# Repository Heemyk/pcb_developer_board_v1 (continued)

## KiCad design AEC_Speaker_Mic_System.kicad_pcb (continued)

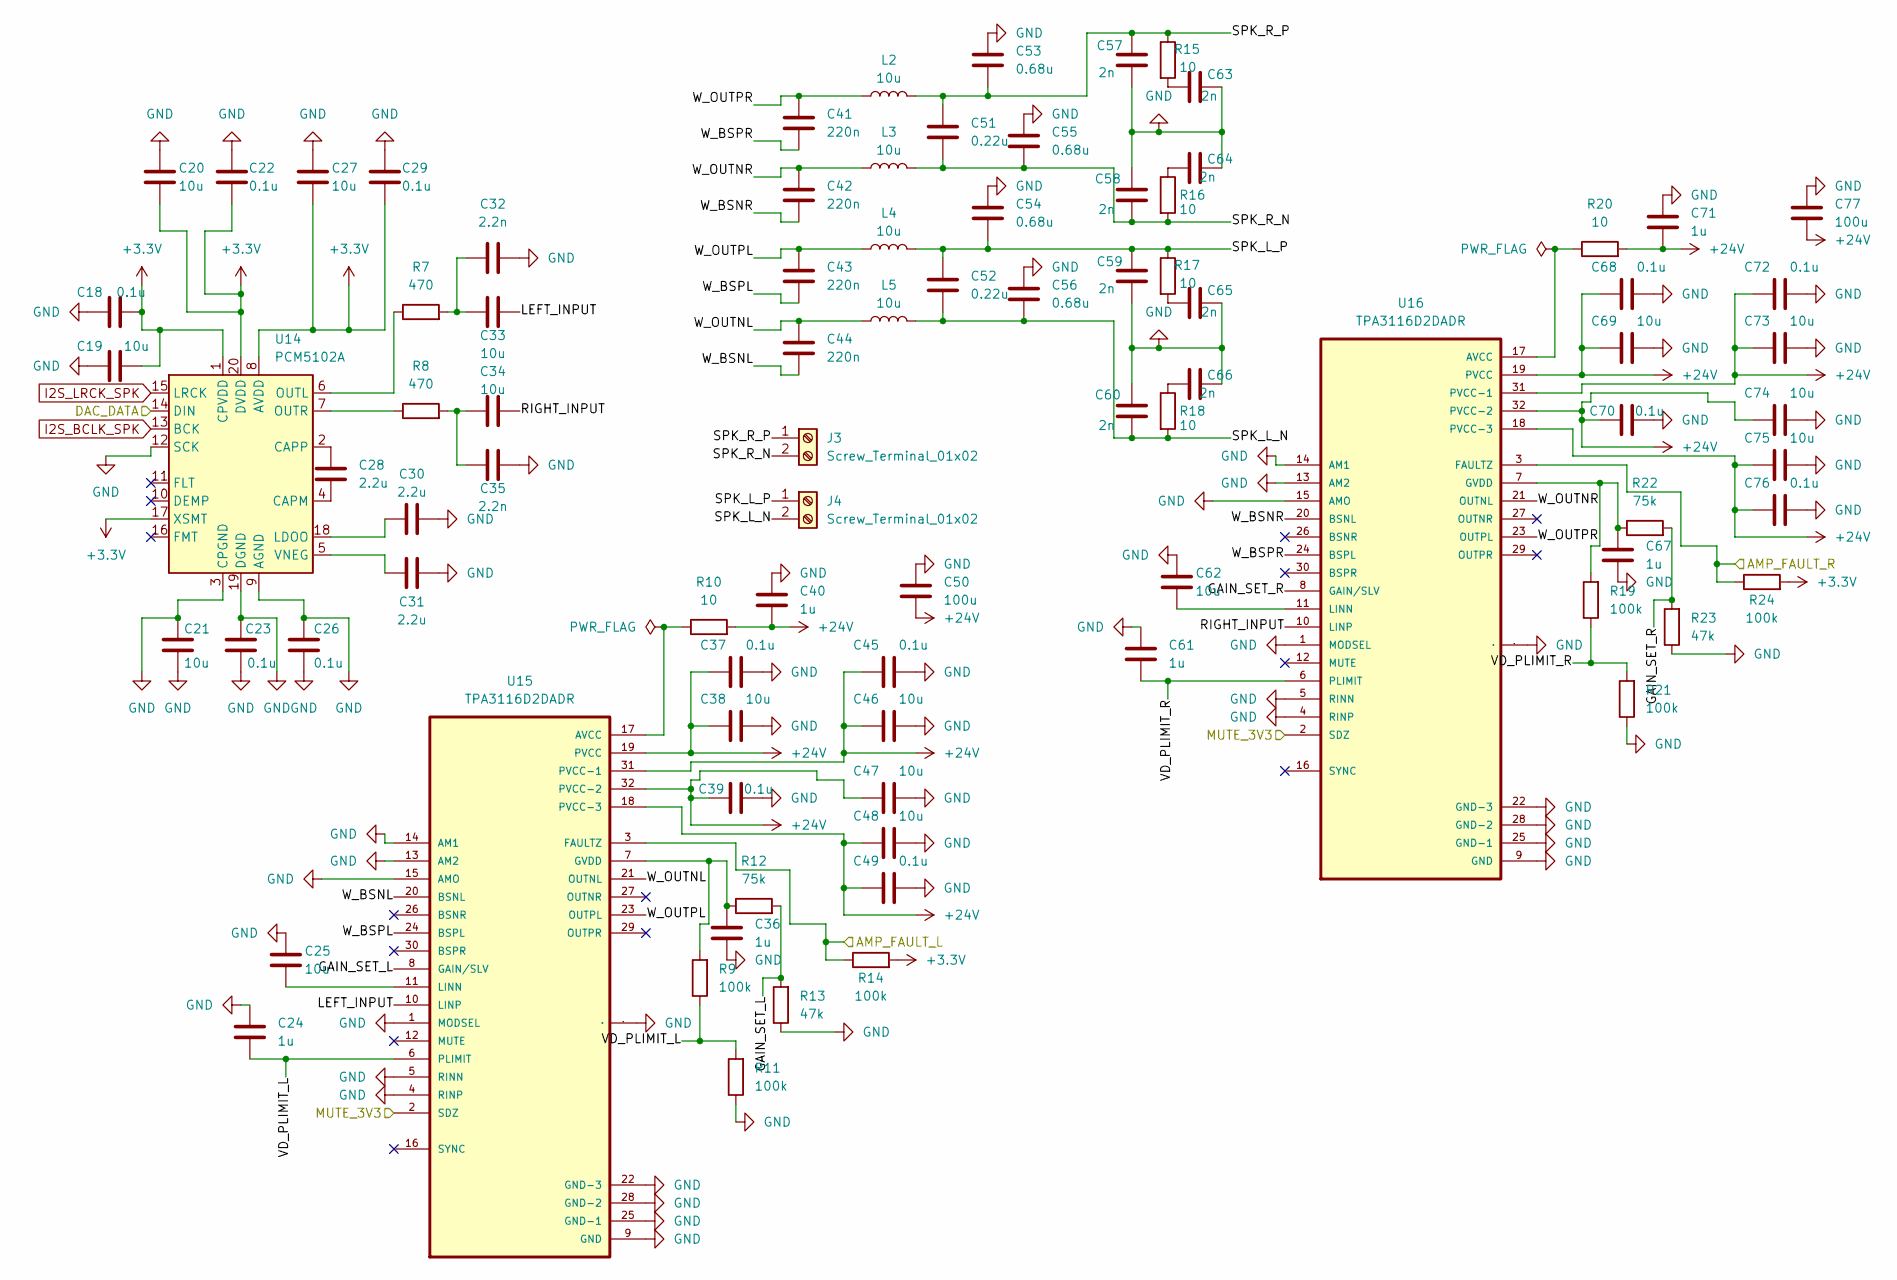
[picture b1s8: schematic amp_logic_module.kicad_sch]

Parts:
C18, C22, C23, C26, C29, C37, C39, C45, C49, C68, C70, C72, C76: 0.1u; C_0603_1608Metric
C19, C20, C21, C25, C27, C33, C34, C38, C46, C47, C48, C62, C69, C73, C74, C75: 10u; C_0603_1608Metric
C24, C36, C40, C61, C67, C71: 1u; C_0603_1608Metric
C28, C30, C31: 2.2u; C_0603_1608Metric
C32, C35: 2.2n; C_0603_1608Metric
C41, C42, C43, C44: 220n; C_0603_1608Metric
C50, C77: 100u; C_0603_1608Metric
C51, C52: 0.22u; C_0603_1608Metric
C53, C54, C55, C56: 0.68u; C_0603_1608Metric
C57, C58, C59, C60, C63, C64, C65, C66: 2n; C_0805_2012Metric; LCSC Part # C1656
J3, J4: Screw_Terminal_01x02; CONN-TH_2P-P5.00_WJ500V-5.08-2P; LCSC Part # C8465
L2: 10u; IND-SMD_L10.4-W10.3; LCSC C9935
L3, L4, L5: 10u; IND-SMD_L10.4-W10.3
R7, R8: 470; R_0603_1608Metric
R9, R11, R14, R19, R21, R24: 100k; R_0603_1608Metric
R10, R15, R16, R17, R18, R20: 10; R_0805_2012Metric
R12, R22: 75k; R_0603_1608Metric
R13: 47k; R_0603_1608Metric
R23: 47k; R_0603_1608Metric; LCSC Part # C25819
U14: PCM5102A; TSSOP-20_4.4x6.5mm_P0.65mm; LCSC Part # C107671
U15, U16: TPA3116D2DADR; SOP65P810X115-33N

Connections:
+3.3V: C18.2, C19.2, C20.2, C22.2, C27.2, C29.2, R14.2, R24.2, U14.1 (CPVDD), U14.8 (AVDD), U14.17 (XSMT), U14.20 (DVDD); also elsewhere on the board
+24V: C37.2, C38.2, C39.2, C40.2, C45.2, C46.2, C47.2, C48.2, C49.2, C50.2, C68.2, C69.2, C70.2, C71.2, C72.2, C73.2, C74.2, C75.2, C76.2, C77.2, R10.2, R20.2, U15.18 (PVCC-3), U15.19 (PVCC), U15.31 (PVCC-1), U15.32 (PVCC-2), U16.18 (PVCC-3), U16.19 (PVCC), U16.31 (PVCC-1), U16.32 (PVCC-2); also elsewhere on the board
/PCB_Control/AMP_FAULT_1: R14.1, U15.3 (FAULTZ); also elsewhere on the board
/PCB_Control/AMP_FAULT_2: R24.1, U16.3 (FAULTZ); also elsewhere on the board
/PCB_Control/Amp_Control_Module_12/GAIN_SET_L: R12.2, R13.2, U15.8 (GAIN/SLV)
/PCB_Control/Amp_Control_Module_12/GAIN_SET_R: R22.2, R23.2, U16.8 (GAIN/SLV)
/PCB_Control/Amp_Control_Module_12/LEFT_INPUT: C33.2, U15.10 (LINP)
/PCB_Control/Amp_Control_Module_12/RIGHT_INPUT: C34.2, U16.10 (LINP)
/PCB_Control/Amp_Control_Module_12/SPK_L_N: C52.2, C56.2, C60.2, J4.2, L5.2, R18.2
/PCB_Control/Amp_Control_Module_12/SPK_L_P: C52.1, C54.2, C59.1, J4.1, L4.2, R17.1
/PCB_Control/Amp_Control_Module_12/SPK_R_N: C51.2, C55.2, C58.2, J3.2, L3.2, R16.2
/PCB_Control/Amp_Control_Module_12/SPK_R_P: C51.1, C53.2, C57.1, J3.1, L2.2, R15.1
/PCB_Control/Amp_Control_Module_12/VD_PLIMIT_L: C24.1, R9.1, R11.2, U15.6 (PLIMIT)
/PCB_Control/Amp_Control_Module_12/VD_PLIMIT_R: C61.1, R19.1, R21.2, U16.6 (PLIMIT)
/PCB_Control/Amp_Control_Module_12/W_BSNL: C44.1, U15.20 (BSNL)
/PCB_Control/Amp_Control_Module_12/W_BSNR: C42.1, U16.20 (BSNL)
/PCB_Control/Amp_Control_Module_12/W_BSPL: C43.1, U15.24 (BSPL)
/PCB_Control/Amp_Control_Module_12/W_BSPR: C41.1, U16.24 (BSPL)
/PCB_Control/Amp_Control_Module_12/W_OUTNL: C44.2, L5.1, U15.21 (OUTNL)
/PCB_Control/Amp_Control_Module_12/W_OUTNR: C42.2, L3.1, U16.21 (OUTNL)
/PCB_Control/Amp_Control_Module_12/W_OUTPL: C43.2, L4.1, U15.23 (OUTPL)
/PCB_Control/Amp_Control_Module_12/W_OUTPR: C41.2, L2.1, U16.23 (OUTPL)
/PCB_Control/DAC_DATA_12: U14.14 (DIN); also elsewhere on the board
/PCB_Control/MUTE_3V3: U15.2 (SDZ), U16.2 (SDZ); also elsewhere on the board
GND: C18.1, C19.1, C20.1, C21.1, C21.2, C22.1, C23.1, C23.2, C24.2, C25.1, C26.1, C26.2, C27.1, C29.1, C30.1, C31.1, C32.2, C35.2, C36.2, C37.1, C38.1, C39.1, C40.1, C45.1, C46.1, C47.1, C48.1, C49.1, C50.1, C53.1, C54.1, C55.1, C56.1, C57.2, C58.1, C59.2, C60.1, C61.2, C62.1, C63.2, C64.2, C65.2, C66.2, C67.2, C68.1, C69.1, C70.1, C71.1, C72.1, C73.1, C74.1, C75.1, C76.1, C77.1, R11.1, R13.1, R21.1, R23.1, U14.3 (CPGND), U14.9 (AGND), U14.12 (SCK), U14.19 (DGND), U15.1 (MODSEL), U15.4 (RINP), U15.5 (RINN), U15.9 (GND), U15.13 (AM2), U15.14 (AM1), U15.15 (AMO), U15.22 (GND-3), U15.25 (GND-1), U15.28 (GND-2), U15.33 (PAD), U16.1 (MODSEL), U16.4 (RINP), U16.5 (RINN), U16.9 (GND), U16.13 (AM2), U16.14 (AM1), U16.15 (AMO), U16.22 (GND-3), U16.25 (GND-1), U16.28 (GND-2), U16.33 (PAD); also elsewhere on the board
I2S_BCLK_SPK: U14.13 (BCK); also elsewhere on the board
I2S_LRCK_SPK: U14.15 (LRCK); also elsewhere on the board
unnamed: C32.1, C33.1, R7.2
unnamed: C34.1, C35.1, R8.2
unnamed: C63.1, R15.2
unnamed: C64.1, R16.1
unnamed: C65.1, R17.2
unnamed: C66.1, R18.1
unnamed: C28.2, U14.4 (CAPM)
unnamed: C28.1, U14.2 (CAPP)
unnamed: C30.2, U14.18 (LDOO)
unnamed: R7.1, U14.6 (OUTL)
unnamed: R8.1, U14.7 (OUTR)
unnamed: C31.2, U14.5 (VNEG)
unnamed: R10.1, U15.17 (AVCC)
unnamed: C36.1, R9.2, R12.1, U15.7 (GVDD)
unnamed: C25.2, U15.11 (LINN)
unnamed: R20.1, U16.17 (AVCC)
unnamed: C67.1, R19.2, R22.1, U16.7 (GVDD)
unnamed: C62.2, U16.11 (LINN)

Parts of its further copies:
C78, C82, C83, C86, C89, C97, C99, C105, C109, C128, C130, C132, C136, C138, C142, C143, C146, C149, C157, C159, C165, C169, C188, C190, C192, C196, C198, C202, C203, C206, C209, C217, C219, C225, C229, C248, C250, C252, C256: 0.1u; C_0603_1608Metric
C79, C80, C81, C85, C87, C93, C94, C98, C106, C107, C108, C122, C129, C133, C134, C135, C139, C140, C141, C145, C147, C153, C154, C158, C166, C167, C168, C182, C189, C193, C194, C195, C199, C200, C201, C205, C207, C213, C214, C218, C226, C227, C228, C242, C249, C253, C254, C255: 10u; C_0603_1608Metric
C84, C96, C100, C121, C127, C131, C144, C156, C160, C181, C187, C191, C204, C216, C220, C241, C247, C251: 1u; C_0603_1608Metric
C88, C90, C91, C148, C150, C151, C208, C210, C211: 2.2u; C_0603_1608Metric
C92, C95, C152, C155, C212, C215: 2.2n; C_0603_1608Metric
C101, C102, C103, C104, C161, C162, C163, C164, C221, C222, C223, C224: 220n; C_0603_1608Metric
C110, C137, C170, C197, C230, C257: 100u; C_0603_1608Metric
C111, C112, C171, C172, C231, C232: 0.22u; C_0603_1608Metric
C113, C114, C115, C116, C173, C174, C175, C176, C233, C234, C235, C236: 0.68u; C_0603_1608Metric
C117, C118, C119, C120, C123, C124, C125, C126, C177, C178, C179, C180, C183, C184, C185, C186, C237, C238, C239, C240, C243, C244, C245, C246: 2n; C_0805_2012Metric; LCSC Part # C1656
J5, J6, J7, J8, J9, J10: Screw_Terminal_01x02; CONN-TH_2P-P5.00_WJ500V-5.08-2P; LCSC Part # C8465
L6, L10, L14: 10u; IND-SMD_L10.4-W10.3; LCSC C9935
L7, L8, L9, L11, L12, L13, L15, L16, L17: 10u; IND-SMD_L10.4-W10.3
R25, R26, R43, R44, R61, R62: 470; R_0603_1608Metric
R27, R29, R32, R37, R39, R42, R45, R47, R50, R55, R57, R60, R63, R65, R68, R73, R75, R78: 100k; R_0603_1608Metric
R28, R33, R34, R35, R36, R38, R46, R51, R52, R53, R54, R56, R64, R69, R70, R71, R72, R74: 10; R_0805_2012Metric
R30, R40, R48, R58, R66, R76: 75k; R_0603_1608Metric
R31, R49, R67: 47k; R_0603_1608Metric
R41, R59, R77: 47k; R_0603_1608Metric; LCSC Part # C25819
U17, U20, U23: PCM5102A; TSSOP-20_4.4x6.5mm_P0.65mm; LCSC Part # C107671
U18, U19, U21, U22, U24, U25: TPA3116D2DADR; SOP65P810X115-33N

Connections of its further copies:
+3.3V: C78.2, C79.2, C80.2, C82.2, C87.2, C89.2, C138.2, C139.2, C140.2, C142.2, C147.2, C149.2, C198.2, C199.2, C200.2, C202.2, C207.2, C209.2, R32.2, R42.2, R50.2, R60.2, R68.2, R78.2, U17.1 (CPVDD), U17.8 (AVDD), U17.17 (XSMT), U17.20 (DVDD), U20.1 (CPVDD), U20.8 (AVDD), U20.17 (XSMT), U20.20 (DVDD), U23.1 (CPVDD), U23.8 (AVDD), U23.17 (XSMT), U23.20 (DVDD); also elsewhere on the board
+24V: C97.2, C98.2, C99.2, C100.2, C105.2, C106.2, C107.2, C108.2, C109.2, C110.2, C128.2, C129.2, C130.2, C131.2, C132.2, C133.2, C134.2, C135.2, C136.2, C137.2, C157.2, C158.2, C159.2, C160.2, C165.2, C166.2, C167.2, C168.2, C169.2, C170.2, C188.2, C189.2, C190.2, C191.2, C192.2, C193.2, C194.2, C195.2, C196.2, C197.2, C217.2, C218.2, C219.2, C220.2, C225.2, C226.2, C227.2, C228.2, C229.2, C230.2, C248.2, C249.2, C250.2, C251.2, C252.2, C253.2, C254.2, C255.2, C256.2, C257.2, R28.2, R38.2, R46.2, R56.2, R64.2, R74.2, U18.18 (PVCC-3), U18.19 (PVCC), U18.31 (PVCC-1), U18.32 (PVCC-2), U19.18 (PVCC-3), U19.19 (PVCC), U19.31 (PVCC-1), U19.32 (PVCC-2), U21.18 (PVCC-3), U21.19 (PVCC), U21.31 (PVCC-1), U21.32 (PVCC-2), U22.18 (PVCC-3), U22.19 (PVCC), U22.31 (PVCC-1), U22.32 (PVCC-2), U24.18 (PVCC-3), U24.19 (PVCC), U24.31 (PVCC-1), U24.32 (PVCC-2), U25.18 (PVCC-3), U25.19 (PVCC), U25.31 (PVCC-1), U25.32 (PVCC-2); also elsewhere on the board
/PCB_Control/AMP_FAULT_3: R32.1, U18.3 (FAULTZ); also elsewhere on the board
/PCB_Control/AMP_FAULT_4: R42.1, U19.3 (FAULTZ); also elsewhere on the board
/PCB_Control/AMP_FAULT_5: R50.1, U21.3 (FAULTZ); also elsewhere on the board
/PCB_Control/AMP_FAULT_6: R60.1, U22.3 (FAULTZ); also elsewhere on the board
/PCB_Control/AMP_FAULT_7: R68.1, U24.3 (FAULTZ); also elsewhere on the board
/PCB_Control/AMP_FAULT_8: R78.1, U25.3 (FAULTZ); also elsewhere on the board
/PCB_Control/Amp_Control_Module_34/GAIN_SET_L: R30.2, R31.2, U18.8 (GAIN/SLV)
/PCB_Control/Amp_Control_Module_34/GAIN_SET_R: R40.2, R41.2, U19.8 (GAIN/SLV)
/PCB_Control/Amp_Control_Module_34/LEFT_INPUT: C93.2, U18.10 (LINP)
/PCB_Control/Amp_Control_Module_34/RIGHT_INPUT: C94.2, U19.10 (LINP)
/PCB_Control/Amp_Control_Module_34/SPK_L_N: C112.2, C116.2, C120.2, J6.2, L9.2, R36.2
/PCB_Control/Amp_Control_Module_34/SPK_L_P: C112.1, C114.2, C119.1, J6.1, L8.2, R35.1
/PCB_Control/Amp_Control_Module_34/SPK_R_N: C111.2, C115.2, C118.2, J5.2, L7.2, R34.2
/PCB_Control/Amp_Control_Module_34/SPK_R_P: C111.1, C113.2, C117.1, J5.1, L6.2, R33.1
/PCB_Control/Amp_Control_Module_34/VD_PLIMIT_L: C84.1, R27.1, R29.2, U18.6 (PLIMIT)
/PCB_Control/Amp_Control_Module_34/VD_PLIMIT_R: C121.1, R37.1, R39.2, U19.6 (PLIMIT)
/PCB_Control/Amp_Control_Module_34/W_BSNL: C104.1, U18.20 (BSNL)
/PCB_Control/Amp_Control_Module_34/W_BSNR: C102.1, U19.20 (BSNL)
/PCB_Control/Amp_Control_Module_34/W_BSPL: C103.1, U18.24 (BSPL)
/PCB_Control/Amp_Control_Module_34/W_BSPR: C101.1, U19.24 (BSPL)
/PCB_Control/Amp_Control_Module_34/W_OUTNL: C104.2, L9.1, U18.21 (OUTNL)
/PCB_Control/Amp_Control_Module_34/W_OUTNR: C102.2, L7.1, U19.21 (OUTNL)
/PCB_Control/Amp_Control_Module_34/W_OUTPL: C103.2, L8.1, U18.23 (OUTPL)
/PCB_Control/Amp_Control_Module_34/W_OUTPR: C101.2, L6.1, U19.23 (OUTPL)
/PCB_Control/Amp_Control_Module_56/GAIN_SET_L: R48.2, R49.2, U21.8 (GAIN/SLV)
/PCB_Control/Amp_Control_Module_56/GAIN_SET_R: R58.2, R59.2, U22.8 (GAIN/SLV)
/PCB_Control/Amp_Control_Module_56/LEFT_INPUT: C153.2, U21.10 (LINP)
/PCB_Control/Amp_Control_Module_56/RIGHT_INPUT: C154.2, U22.10 (LINP)
/PCB_Control/Amp_Control_Module_56/SPK_L_N: C172.2, C176.2, C180.2, J8.2, L13.2, R54.2
/PCB_Control/Amp_Control_Module_56/SPK_L_P: C172.1, C174.2, C179.1, J8.1, L12.2, R53.1
/PCB_Control/Amp_Control_Module_56/SPK_R_N: C171.2, C175.2, C178.2, J7.2, L11.2, R52.2
/PCB_Control/Amp_Control_Module_56/SPK_R_P: C171.1, C173.2, C177.1, J7.1, L10.2, R51.1
/PCB_Control/Amp_Control_Module_56/VD_PLIMIT_L: C144.1, R45.1, R47.2, U21.6 (PLIMIT)
/PCB_Control/Amp_Control_Module_56/VD_PLIMIT_R: C181.1, R55.1, R57.2, U22.6 (PLIMIT)
/PCB_Control/Amp_Control_Module_56/W_BSNL: C164.1, U21.20 (BSNL)
/PCB_Control/Amp_Control_Module_56/W_BSNR: C162.1, U22.20 (BSNL)
/PCB_Control/Amp_Control_Module_56/W_BSPL: C163.1, U21.24 (BSPL)
/PCB_Control/Amp_Control_Module_56/W_BSPR: C161.1, U22.24 (BSPL)
/PCB_Control/Amp_Control_Module_56/W_OUTNL: C164.2, L13.1, U21.21 (OUTNL)
/PCB_Control/Amp_Control_Module_56/W_OUTNR: C162.2, L11.1, U22.21 (OUTNL)
/PCB_Control/Amp_Control_Module_56/W_OUTPL: C163.2, L12.1, U21.23 (OUTPL)
/PCB_Control/Amp_Control_Module_56/W_OUTPR: C161.2, L10.1, U22.23 (OUTPL)
/PCB_Control/Amp_Control_Module_78/GAIN_SET_L: R66.2, R67.2, U24.8 (GAIN/SLV)
/PCB_Control/Amp_Control_Module_78/GAIN_SET_R: R76.2, R77.2, U25.8 (GAIN/SLV)
/PCB_Control/Amp_Control_Module_78/LEFT_INPUT: C213.2, U24.10 (LINP)
/PCB_Control/Amp_Control_Module_78/RIGHT_INPUT: C214.2, U25.10 (LINP)
/PCB_Control/Amp_Control_Module_78/SPK_L_N: C232.2, C236.2, C240.2, J10.2, L17.2, R72.2
/PCB_Control/Amp_Control_Module_78/SPK_L_P: C232.1, C234.2, C239.1, J10.1, L16.2, R71.1
/PCB_Control/Amp_Control_Module_78/SPK_R_N: C231.2, C235.2, C238.2, J9.2, L15.2, R70.2
/PCB_Control/Amp_Control_Module_78/SPK_R_P: C231.1, C233.2, C237.1, J9.1, L14.2, R69.1
/PCB_Control/Amp_Control_Module_78/VD_PLIMIT_L: C204.1, R63.1, R65.2, U24.6 (PLIMIT)
/PCB_Control/Amp_Control_Module_78/VD_PLIMIT_R: C241.1, R73.1, R75.2, U25.6 (PLIMIT)
/PCB_Control/Amp_Control_Module_78/W_BSNL: C224.1, U24.20 (BSNL)
/PCB_Control/Amp_Control_Module_78/W_BSNR: C222.1, U25.20 (BSNL)
/PCB_Control/Amp_Control_Module_78/W_BSPL: C223.1, U24.24 (BSPL)
/PCB_Control/Amp_Control_Module_78/W_BSPR: C221.1, U25.24 (BSPL)
/PCB_Control/Amp_Control_Module_78/W_OUTNL: C224.2, L17.1, U24.21 (OUTNL)
/PCB_Control/Amp_Control_Module_78/W_OUTNR: C222.2, L15.1, U25.21 (OUTNL)
/PCB_Control/Amp_Control_Module_78/W_OUTPL: C223.2, L16.1, U24.23 (OUTPL)
/PCB_Control/Amp_Control_Module_78/W_OUTPR: C221.2, L14.1, U25.23 (OUTPL)
/PCB_Control/DAC_DATA_34: U17.14 (DIN); also elsewhere on the board
/PCB_Control/DAC_DATA_56: U20.14 (DIN); also elsewhere on the board
/PCB_Control/DAC_DATA_78: U23.14 (DIN); also elsewhere on the board
/PCB_Control/MUTE_3V3: U18.2 (SDZ), U19.2 (SDZ), U21.2 (SDZ), U22.2 (SDZ), U24.2 (SDZ), U25.2 (SDZ); also elsewhere on the board
GND: C78.1, C79.1, C80.1, C81.1, C81.2, C82.1, C83.1, C83.2, C84.2, C85.1, C86.1, C86.2, C87.1, C89.1, C90.1, C91.1, C92.2, C95.2, C96.2, C97.1, C98.1, C99.1, C100.1, C105.1, C106.1, C107.1, C108.1, C109.1, C110.1, C113.1, C114.1, C115.1, C116.1, C117.2, C118.1, C119.2, C120.1, C121.2, C122.1, C123.2, C124.2, C125.2, C126.2, C127.2, C128.1, C129.1, C130.1, C131.1, C132.1, C133.1, C134.1, C135.1, C136.1, C137.1, C138.1, C139.1, C140.1, C141.1, C141.2, C142.1, C143.1, C143.2, C144.2, C145.1, C146.1, C146.2, C147.1, C149.1, C150.1, C151.1, C152.2, C155.2, C156.2, C157.1, C158.1, C159.1, C160.1, C165.1, C166.1, C167.1, C168.1, C169.1, C170.1, C173.1, C174.1, C175.1, C176.1, C177.2, C178.1, C179.2, C180.1, C181.2, C182.1, C183.2, C184.2, C185.2, C186.2, C187.2, C188.1, C189.1, C190.1, C191.1, C192.1, C193.1, C194.1, C195.1, C196.1, C197.1, C198.1, C199.1, C200.1, C201.1, C201.2, C202.1, C203.1, C203.2, C204.2, C205.1, C206.1, C206.2, C207.1, C209.1, C210.1, C211.1, C212.2, C215.2, C216.2, C217.1, C218.1, C219.1, C220.1, C225.1, C226.1, C227.1, C228.1, C229.1, C230.1, C233.1, C234.1, C235.1, C236.1, C237.2, C238.1, C239.2, C240.1, C241.2, C242.1, C243.2, C244.2, C245.2, C246.2, C247.2, C248.1, C249.1, C250.1, C251.1, C252.1, C253.1, C254.1, C255.1, C256.1, C257.1, R29.1, R31.1, R39.1, R41.1, R47.1, R49.1, R57.1, R59.1, R65.1, R67.1, R75.1, R77.1, U17.3 (CPGND), U17.9 (AGND), U17.12 (SCK), U17.19 (DGND), U18.1 (MODSEL), U18.4 (RINP), U18.5 (RINN), U18.9 (GND), U18.13 (AM2), U18.14 (AM1), U18.15 (AMO), U18.22 (GND-3), U18.25 (GND-1), U18.28 (GND-2), U18.33 (PAD), U19.1 (MODSEL), U19.4 (RINP), U19.5 (RINN), U19.9 (GND), U19.13 (AM2), U19.14 (AM1), U19.15 (AMO), U19.22 (GND-3), U19.25 (GND-1), U19.28 (GND-2), U19.33 (PAD), U20.3 (CPGND), U20.9 (AGND), U20.12 (SCK), U20.19 (DGND), U21.1 (MODSEL), U21.4 (RINP), U21.5 (RINN), U21.9 (GND), U21.13 (AM2), U21.14 (AM1), U21.15 (AMO), U21.22 (GND-3), U21.25 (GND-1), U21.28 (GND-2), U21.33 (PAD), U22.1 (MODSEL), U22.4 (RINP), U22.5 (RINN), U22.9 (GND), U22.13 (AM2), U22.14 (AM1), U22.15 (AMO), U22.22 (GND-3), U22.25 (GND-1), U22.28 (GND-2), U22.33 (PAD), U23.3 (CPGND), U23.9 (AGND), U23.12 (SCK), U23.19 (DGND), U24.1 (MODSEL), U24.4 (RINP), U24.5 (RINN), U24.9 (GND), U24.13 (AM2), U24.14 (AM1), U24.15 (AMO), U24.22 (GND-3), U24.25 (GND-1), U24.28 (GND-2), U24.33 (PAD), U25.1 (MODSEL), U25.4 (RINP), U25.5 (RINN), U25.9 (GND), U25.13 (AM2), U25.14 (AM1), U25.15 (AMO), U25.22 (GND-3), U25.25 (GND-1), U25.28 (GND-2), U25.33 (PAD); also elsewhere on the board
I2S_BCLK_SPK: U17.13 (BCK), U20.13 (BCK), U23.13 (BCK); also elsewhere on the board
I2S_LRCK_SPK: U17.15 (LRCK), U20.15 (LRCK), U23.15 (LRCK); also elsewhere on the board
unnamed: C92.1, C93.1, R25.2
unnamed: C94.1, C95.1, R26.2
unnamed: C123.1, R33.2
unnamed: C124.1, R34.1
unnamed: C125.1, R35.2
unnamed: C126.1, R36.1
unnamed: C152.1, C153.1, R43.2
unnamed: C154.1, C155.1, R44.2
unnamed: C183.1, R51.2
unnamed: C184.1, R52.1
unnamed: C185.1, R53.2
unnamed: C186.1, R54.1
unnamed: C212.1, C213.1, R61.2
unnamed: C214.1, C215.1, R62.2
unnamed: C243.1, R69.2
unnamed: C244.1, R70.1
unnamed: C245.1, R71.2
unnamed: C246.1, R72.1
unnamed: C88.2, U17.4 (CAPM)
unnamed: C88.1, U17.2 (CAPP)
unnamed: C90.2, U17.18 (LDOO)
unnamed: R25.1, U17.6 (OUTL)
unnamed: R26.1, U17.7 (OUTR)
unnamed: C91.2, U17.5 (VNEG)
unnamed: R28.1, U18.17 (AVCC)
unnamed: C96.1, R27.2, R30.1, U18.7 (GVDD)
unnamed: C85.2, U18.11 (LINN)
unnamed: R38.1, U19.17 (AVCC)
unnamed: C127.1, R37.2, R40.1, U19.7 (GVDD)
unnamed: C122.2, U19.11 (LINN)
unnamed: C148.2, U20.4 (CAPM)
unnamed: C148.1, U20.2 (CAPP)
unnamed: C150.2, U20.18 (LDOO)
unnamed: R43.1, U20.6 (OUTL)
unnamed: R44.1, U20.7 (OUTR)
unnamed: C151.2, U20.5 (VNEG)
unnamed: R46.1, U21.17 (AVCC)
unnamed: C156.1, R45.2, R48.1, U21.7 (GVDD)
unnamed: C145.2, U21.11 (LINN)
unnamed: R56.1, U22.17 (AVCC)
unnamed: C187.1, R55.2, R58.1, U22.7 (GVDD)
unnamed: C182.2, U22.11 (LINN)
unnamed: C208.2, U23.4 (CAPM)
unnamed: C208.1, U23.2 (CAPP)
unnamed: C210.2, U23.18 (LDOO)
unnamed: R61.1, U23.6 (OUTL)
unnamed: R62.1, U23.7 (OUTR)
unnamed: C211.2, U23.5 (VNEG)
unnamed: R64.1, U24.17 (AVCC)
unnamed: C216.1, R63.2, R66.1, U24.7 (GVDD)
unnamed: C205.2, U24.11 (LINN)
unnamed: R74.1, U25.17 (AVCC)
unnamed: C247.1, R73.2, R76.1, U25.7 (GVDD)
unnamed: C242.2, U25.11 (LINN)

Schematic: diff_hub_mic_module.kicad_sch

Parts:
C14: 0.1u; C_0603_1608Metric
U6: RJ45; RJ45-SMD_HC-RJ45-055-4_2; Manufacturer Part HC-RJ45-055-4; LCSC Part Name 沉板 不带LED
U7: MAX3485_SD; SOIC-8_3.9x4.9mm_P1.27mm

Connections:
+3.3V: C14.2, U7.8 (VCC); also elsewhere on the board
+5V: U6.8; also elsewhere on the board
/Hub_Main/BCLK_N: U6.5; also elsewhere on the board
/Hub_Main/BCLK_P: U6.6; also elsewhere on the board
/Hub_Main/DATA_3V3_1: U7.1 (RO); also elsewhere on the board
/Hub_Main/Hub_Mic_Module_1/DATA_N: U6.1, U7.7 (B)
/Hub_Main/Hub_Mic_Module_1/DATA_P: U6.2, U7.6 (A)
/Hub_Main/LRCK_N: U6.3; also elsewhere on the board
/Hub_Main/LRCK_P: U6.4; also elsewhere on the board
GND: C14.1, U6.7, U6.9, U6.10, U7.5 (GND); also elsewhere on the board
MIC_EN: U7.2 (~RE), U7.3 (DE); also elsewhere on the board

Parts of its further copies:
C15, C16, C17: 0.1u; C_0603_1608Metric
U8, U10, U12: RJ45; RJ45-SMD_HC-RJ45-055-4_2; Manufacturer Part HC-RJ45-055-4; LCSC Part Name 沉板 不带LED
U9, U11, U13: MAX3485_SD; SOIC-8_3.9x4.9mm_P1.27mm

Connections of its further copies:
+3.3V: C15.2, C16.2, C17.2, U9.8 (VCC), U11.8 (VCC), U13.8 (VCC); also elsewhere on the board
+5V: U8.8, U10.8, U12.8; also elsewhere on the board
/Hub_Main/BCLK_N: U8.5, U10.5, U12.5; also elsewhere on the board
/Hub_Main/BCLK_P: U8.6, U10.6, U12.6; also elsewhere on the board
/Hub_Main/DATA_3V3_2: U9.1 (RO); also elsewhere on the board
/Hub_Main/DATA_3V3_3: U11.1 (RO); also elsewhere on the board
/Hub_Main/DATA_3V3_4: U13.1 (RO); also elsewhere on the board
/Hub_Main/Hub_Mic_Module_2/DATA_N: U8.1, U9.7 (B)
/Hub_Main/Hub_Mic_Module_2/DATA_P: U8.2, U9.6 (A)
/Hub_Main/Hub_Mic_Module_3/DATA_N: U10.1, U11.7 (B)
/Hub_Main/Hub_Mic_Module_3/DATA_P: U10.2, U11.6 (A)
/Hub_Main/Hub_Mic_Module_4/DATA_N: U12.1, U13.7 (B)
/Hub_Main/Hub_Mic_Module_4/DATA_P: U12.2, U13.6 (A)
/Hub_Main/LRCK_N: U8.3, U10.3, U12.3; also elsewhere on the board
/Hub_Main/LRCK_P: U8.4, U10.4, U12.4; also elsewhere on the board
GND: C15.1, C16.1, C17.1, U8.7, U8.9, U8.10, U9.5 (GND), U10.7, U10.9, U10.10, U11.5 (GND), U12.7, U12.9, U12.10, U13.5 (GND); also elsewhere on the board
MIC_EN: U9.2 (~RE), U9.3 (DE), U11.2 (~RE), U11.3 (DE), U13.2 (~RE), U13.3 (DE); also elsewhere on the board

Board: 2 copper layers, 526 parts (0 on the bottom side), 301 nets, no tracks yet.

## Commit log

2026-01-11 Added some fan safety
2026-01-11 Fixed most ERC checks
2026-01-11 Cleared ERCs, need to footprint and switch THT for SMD
2026-01-13 Footprinting done (warnings on schematic side but pcb import works fine)
2026-01-14 Minor schematic changes
2026-01-14 Added footprints to repo
